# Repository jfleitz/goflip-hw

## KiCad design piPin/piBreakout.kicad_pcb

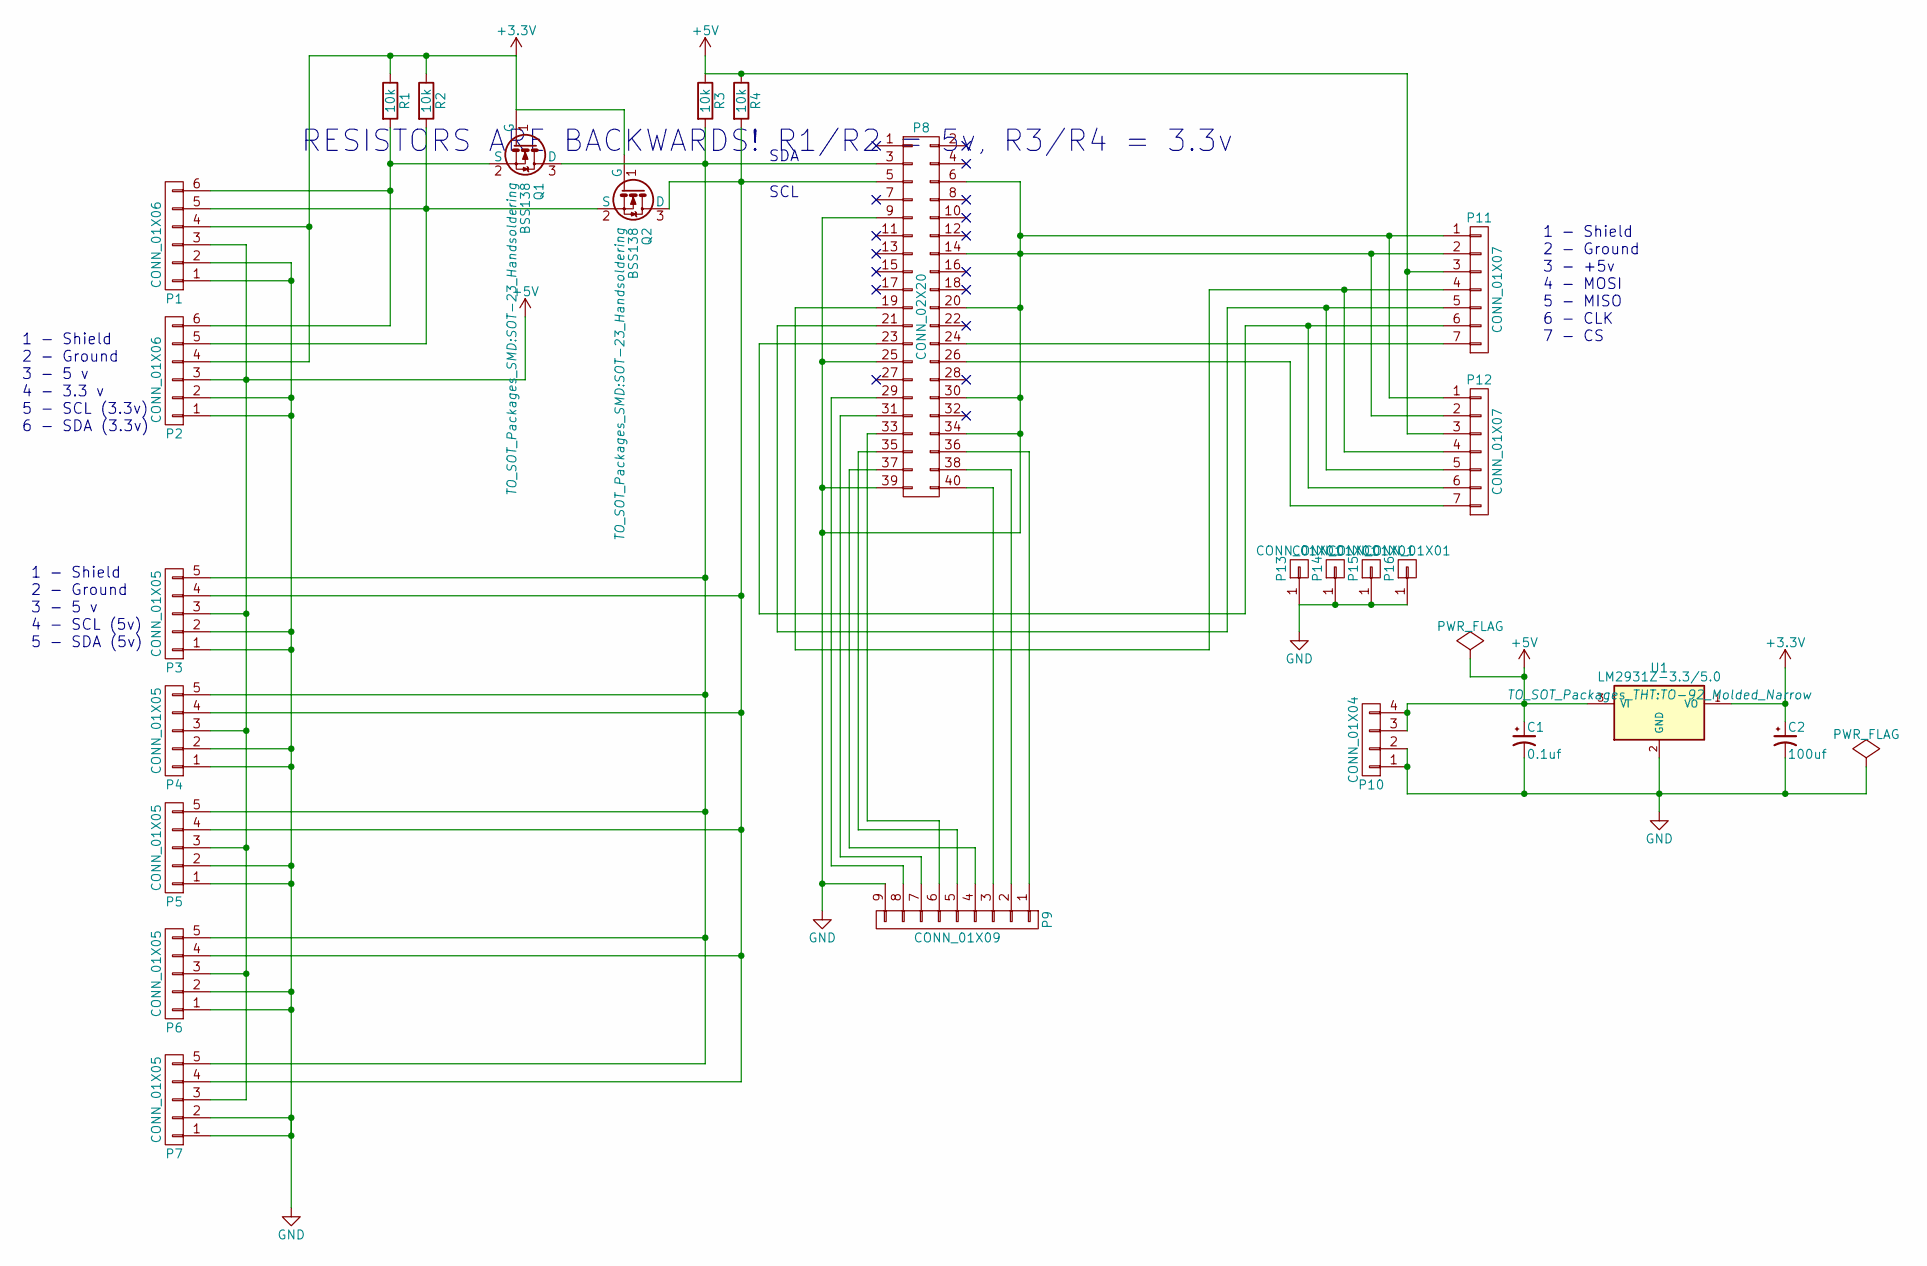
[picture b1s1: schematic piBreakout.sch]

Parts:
C1: 0.1uf; C_Radial_D5_L11_P2
C2: 100uf; C_Radial_D5_L11_P2
P1, P2: CONN_01X06; Molex_KK_6410-06
P3, P4, P5, P6, P7: CONN_01X05; Molex_KK_6410-05
P8: CONN_02X20; IDC_Header_Straight_40pins
P9: CONN_01X09; Molex_KK_6410-09
P10: CONN_01X04; Molex_KK_6410-04
P11, P12: CONN_01X07; Molex_KK_6410-07
P13, P14, P15, P16: CONN_01X01; 1pin
Q1, Q2: BSS138; SOT-23_Handsoldering
R1, R2, R3, R4: 10k; Resistor_Horizontal_RM15mm
U1: LM2931Z-3.3/5.0; TO-92_Molded_Narrow

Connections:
+3V3: C2.1, P1.4, P2.4, Q1.1 (G), Q2.1 (G), R1.1, R2.1, U1.1 (VO)
+5V: C1.1, P1.3, P2.3, P3.3, P4.3, P5.3, P6.3, P7.3, P10.3, P10.4, P11.3, P12.3, R3.1, R4.1, U1.3 (VI); also elsewhere on the board
GND: C1.2, C2.2, P1.1, P1.2, P2.1, P2.2, P3.1, P3.2, P4.1, P4.2, P5.1, P5.2, P6.1, P6.2, P7.1, P7.2, P8.6, P8.9, P8.14, P8.20, P8.25, P8.30, P8.34, P8.39, P9.9, P10.1, P10.2, P11.1, P11.2, P12.1, P12.2, P13.1, P14.1, P15.1, P16.1, U1.2 (GND); also elsewhere on the board
unnamed: P1.5, P2.5, Q2.2 (S), R2.2
unnamed: P1.6, P2.6, Q1.2 (S), R1.2
unnamed: P3.4, P4.4, P5.4, P6.4, P7.4, P8.5, Q2.3 (D), R4.2
unnamed: P3.5, P4.5, P5.5, P6.5, P7.5, P8.3, Q1.3 (D), R3.2
unnamed 23: P8.29, P9.8; also elsewhere on the board
unnamed 24: P8.31, P9.7; also elsewhere on the board
unnamed 26: P8.33, P9.6; also elsewhere on the board
unnamed 27: P8.35, P9.5; also elsewhere on the board
unnamed 28: P8.36, P9.1; also elsewhere on the board
unnamed 29: P8.37, P9.4; also elsewhere on the board
unnamed 30: P8.38, P9.2; also elsewhere on the board
unnamed 31: P8.40, P9.3; also elsewhere on the board
unnamed: P8.19, P11.4, P12.4
unnamed: P8.21, P11.5, P12.5
unnamed: P8.23, P11.6, P12.6
unnamed: P8.24, P11.7
unnamed: P8.26, P12.7

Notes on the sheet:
1 - Shield 2 - Ground 3 - +5v 4 - MOSI 5 - MISO 6 - CLK 7 - CS
1 - Shield 2 - Ground 3 - 5 v 4 - 3.3 v 5 - SCL (3.3v) 6 - SDA (3.3v)
1 - Shield 2 - Ground 3 - 5 v 4 - SCL (5v) 5 - SDA (5v)
SDA
SCL
RESISTORS ARE BACKWARDS! R1/R2 = 5v, R3/R4 = 3.3v

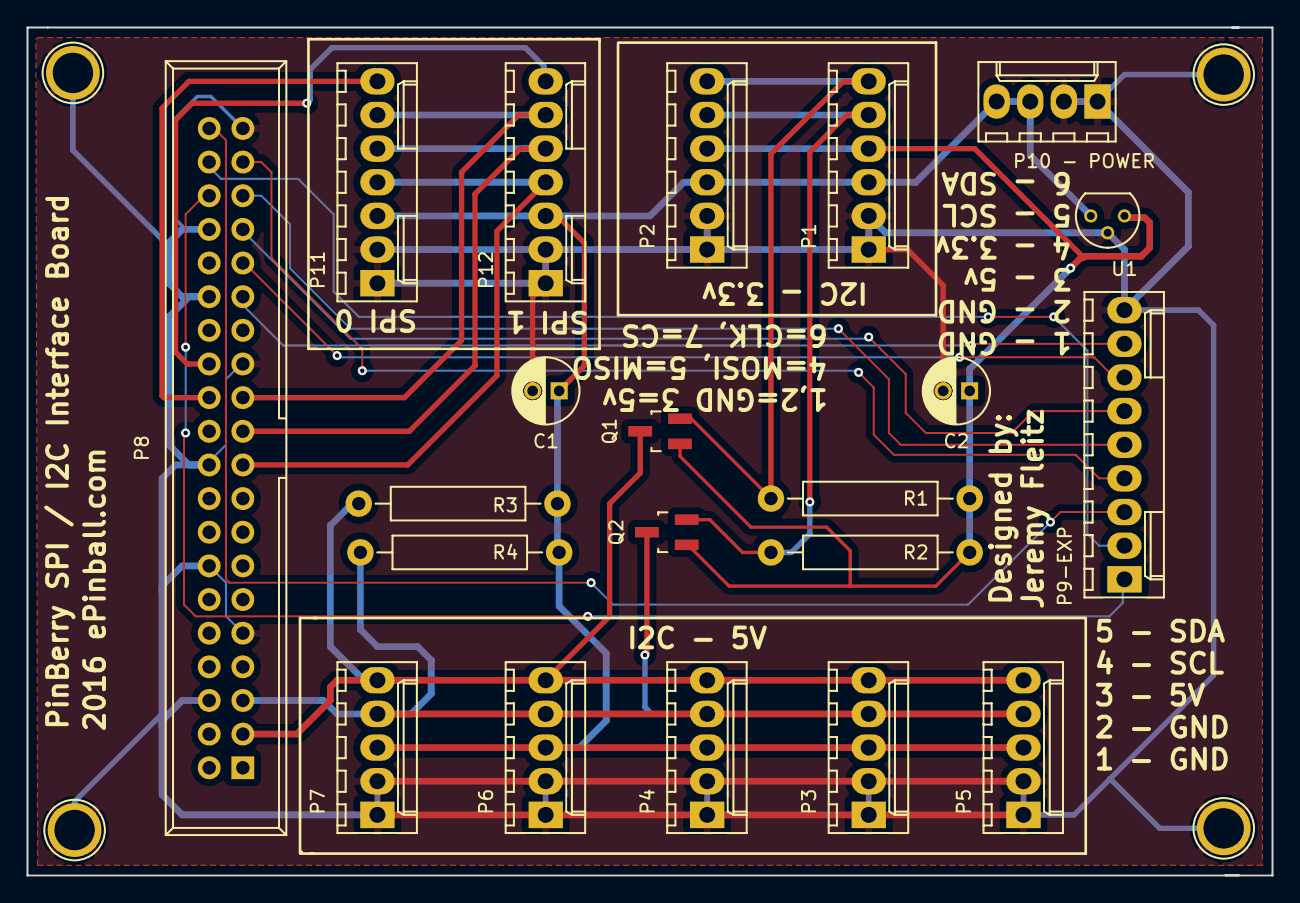
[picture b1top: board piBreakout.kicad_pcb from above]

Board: 2 copper layers, 94.0 x 64.0 mm, 25 parts (0 on the bottom side), 20 nets.

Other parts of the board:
P9-EXP: CONN_01X09; Molex_KK_6410-09
P10 - POWER: POWER; Molex_KK_6410-04

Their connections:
+5V: P10 - POWER.3, P10 - POWER.4; also elsewhere on the board
GND: P9-EXP.9, P10 - POWER.1, P10 - POWER.2; also elsewhere on the board
unnamed 23: P9-EXP.8; also elsewhere on the board
unnamed 24: P9-EXP.7; also elsewhere on the board
unnamed 26: P9-EXP.6; also elsewhere on the board
unnamed 27: P9-EXP.5; also elsewhere on the board
unnamed 28: P9-EXP.1; also elsewhere on the board
unnamed 29: P9-EXP.4; also elsewhere on the board
unnamed 30: P9-EXP.2; also elsewhere on the board
unnamed 31: P9-EXP.3; also elsewhere on the board

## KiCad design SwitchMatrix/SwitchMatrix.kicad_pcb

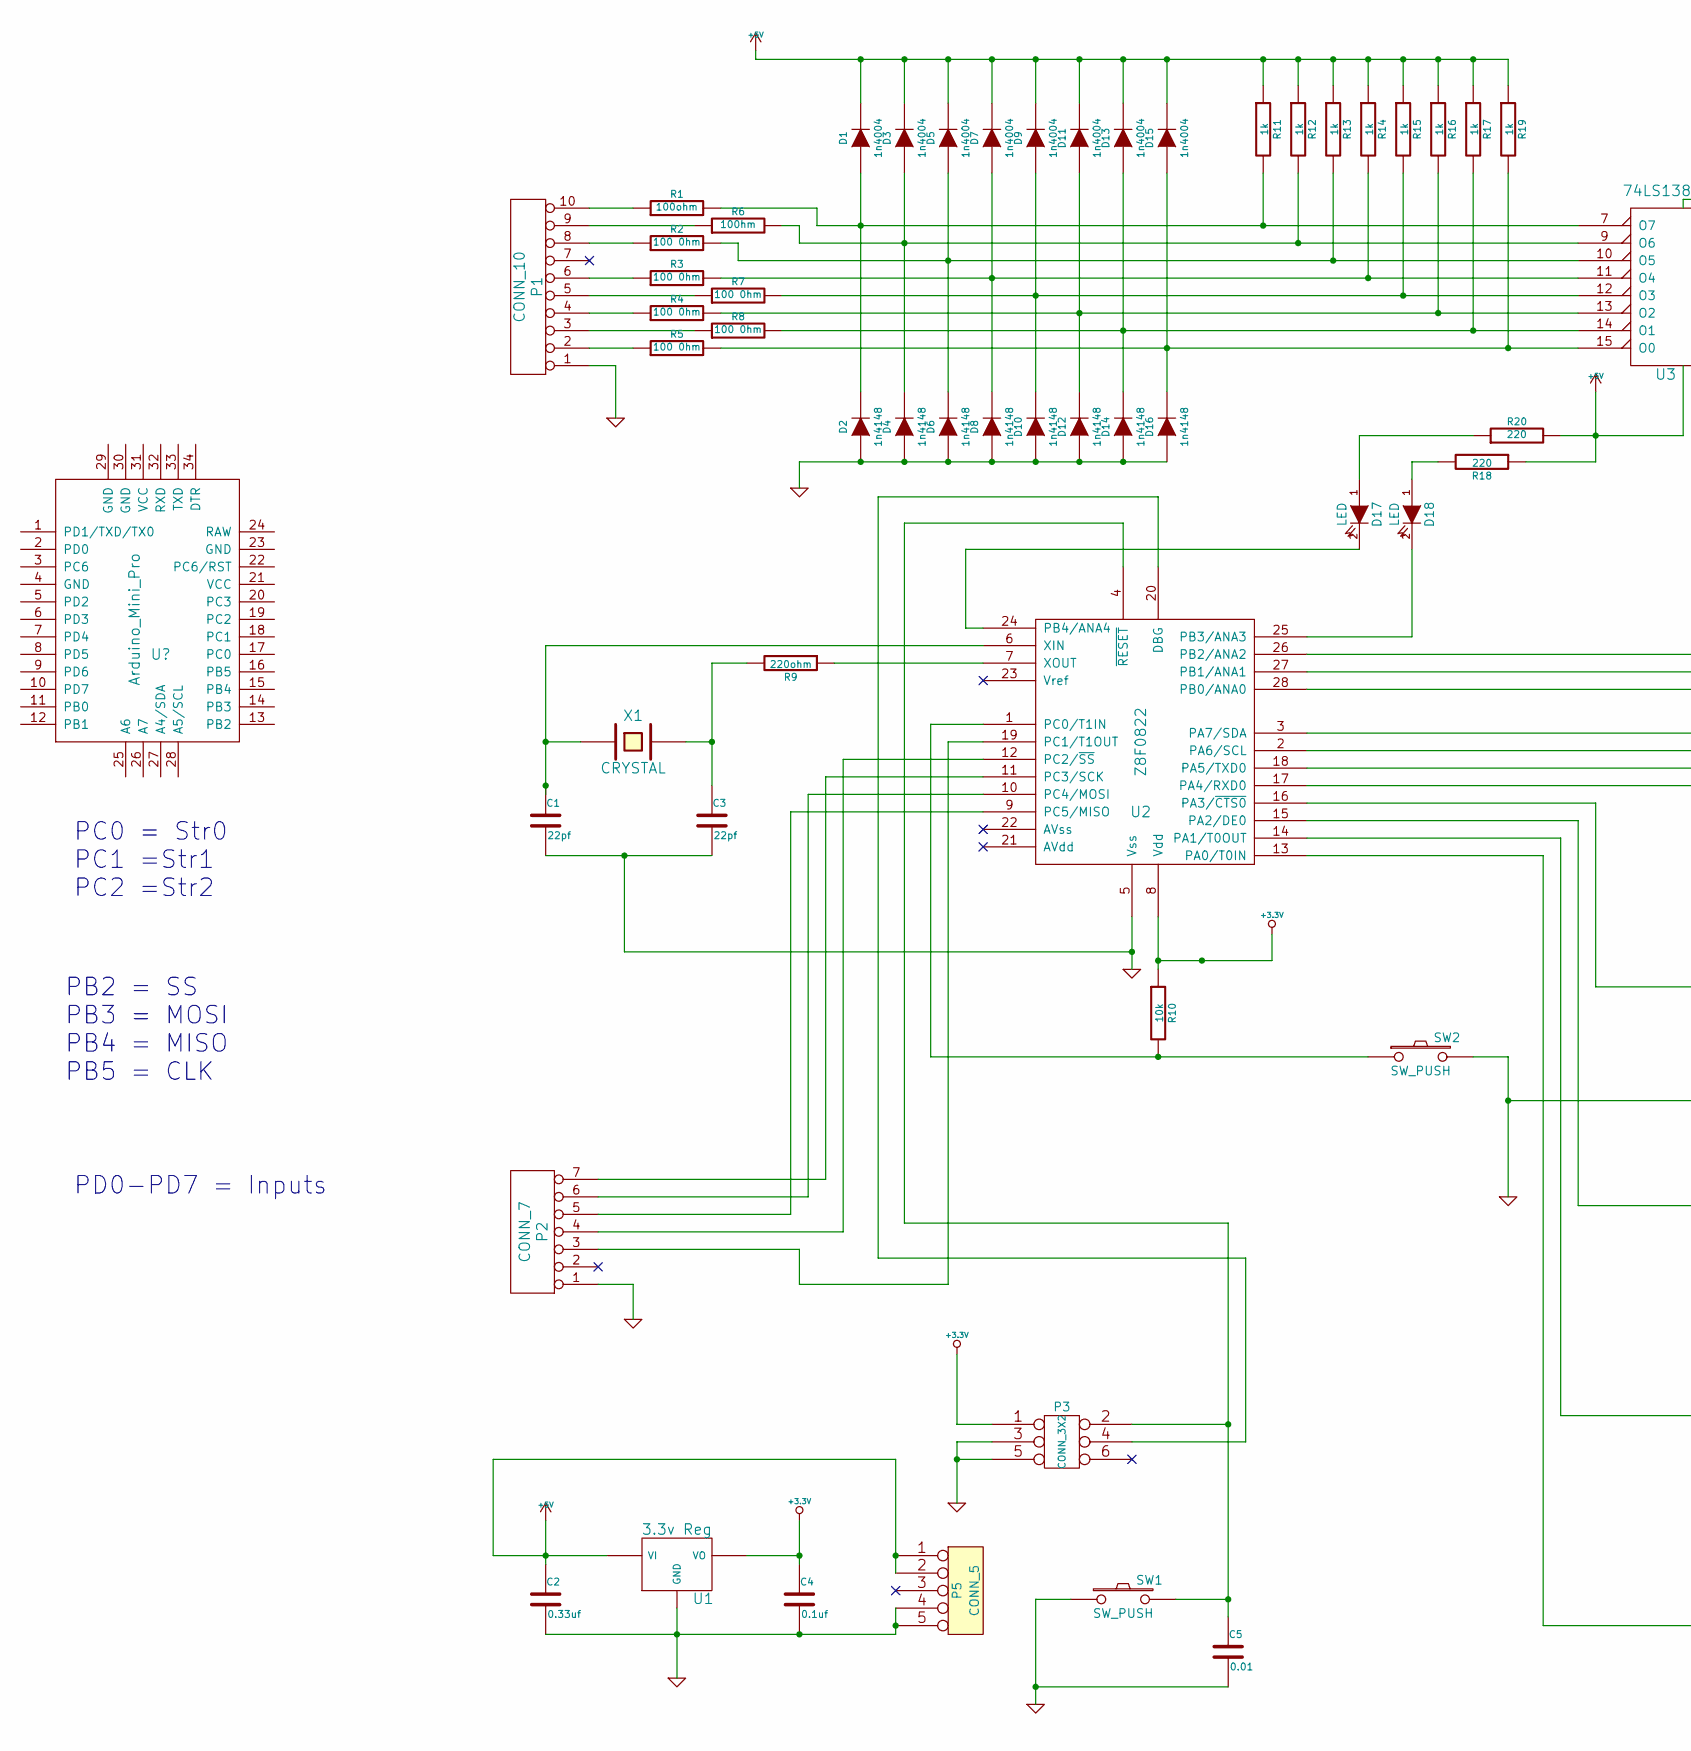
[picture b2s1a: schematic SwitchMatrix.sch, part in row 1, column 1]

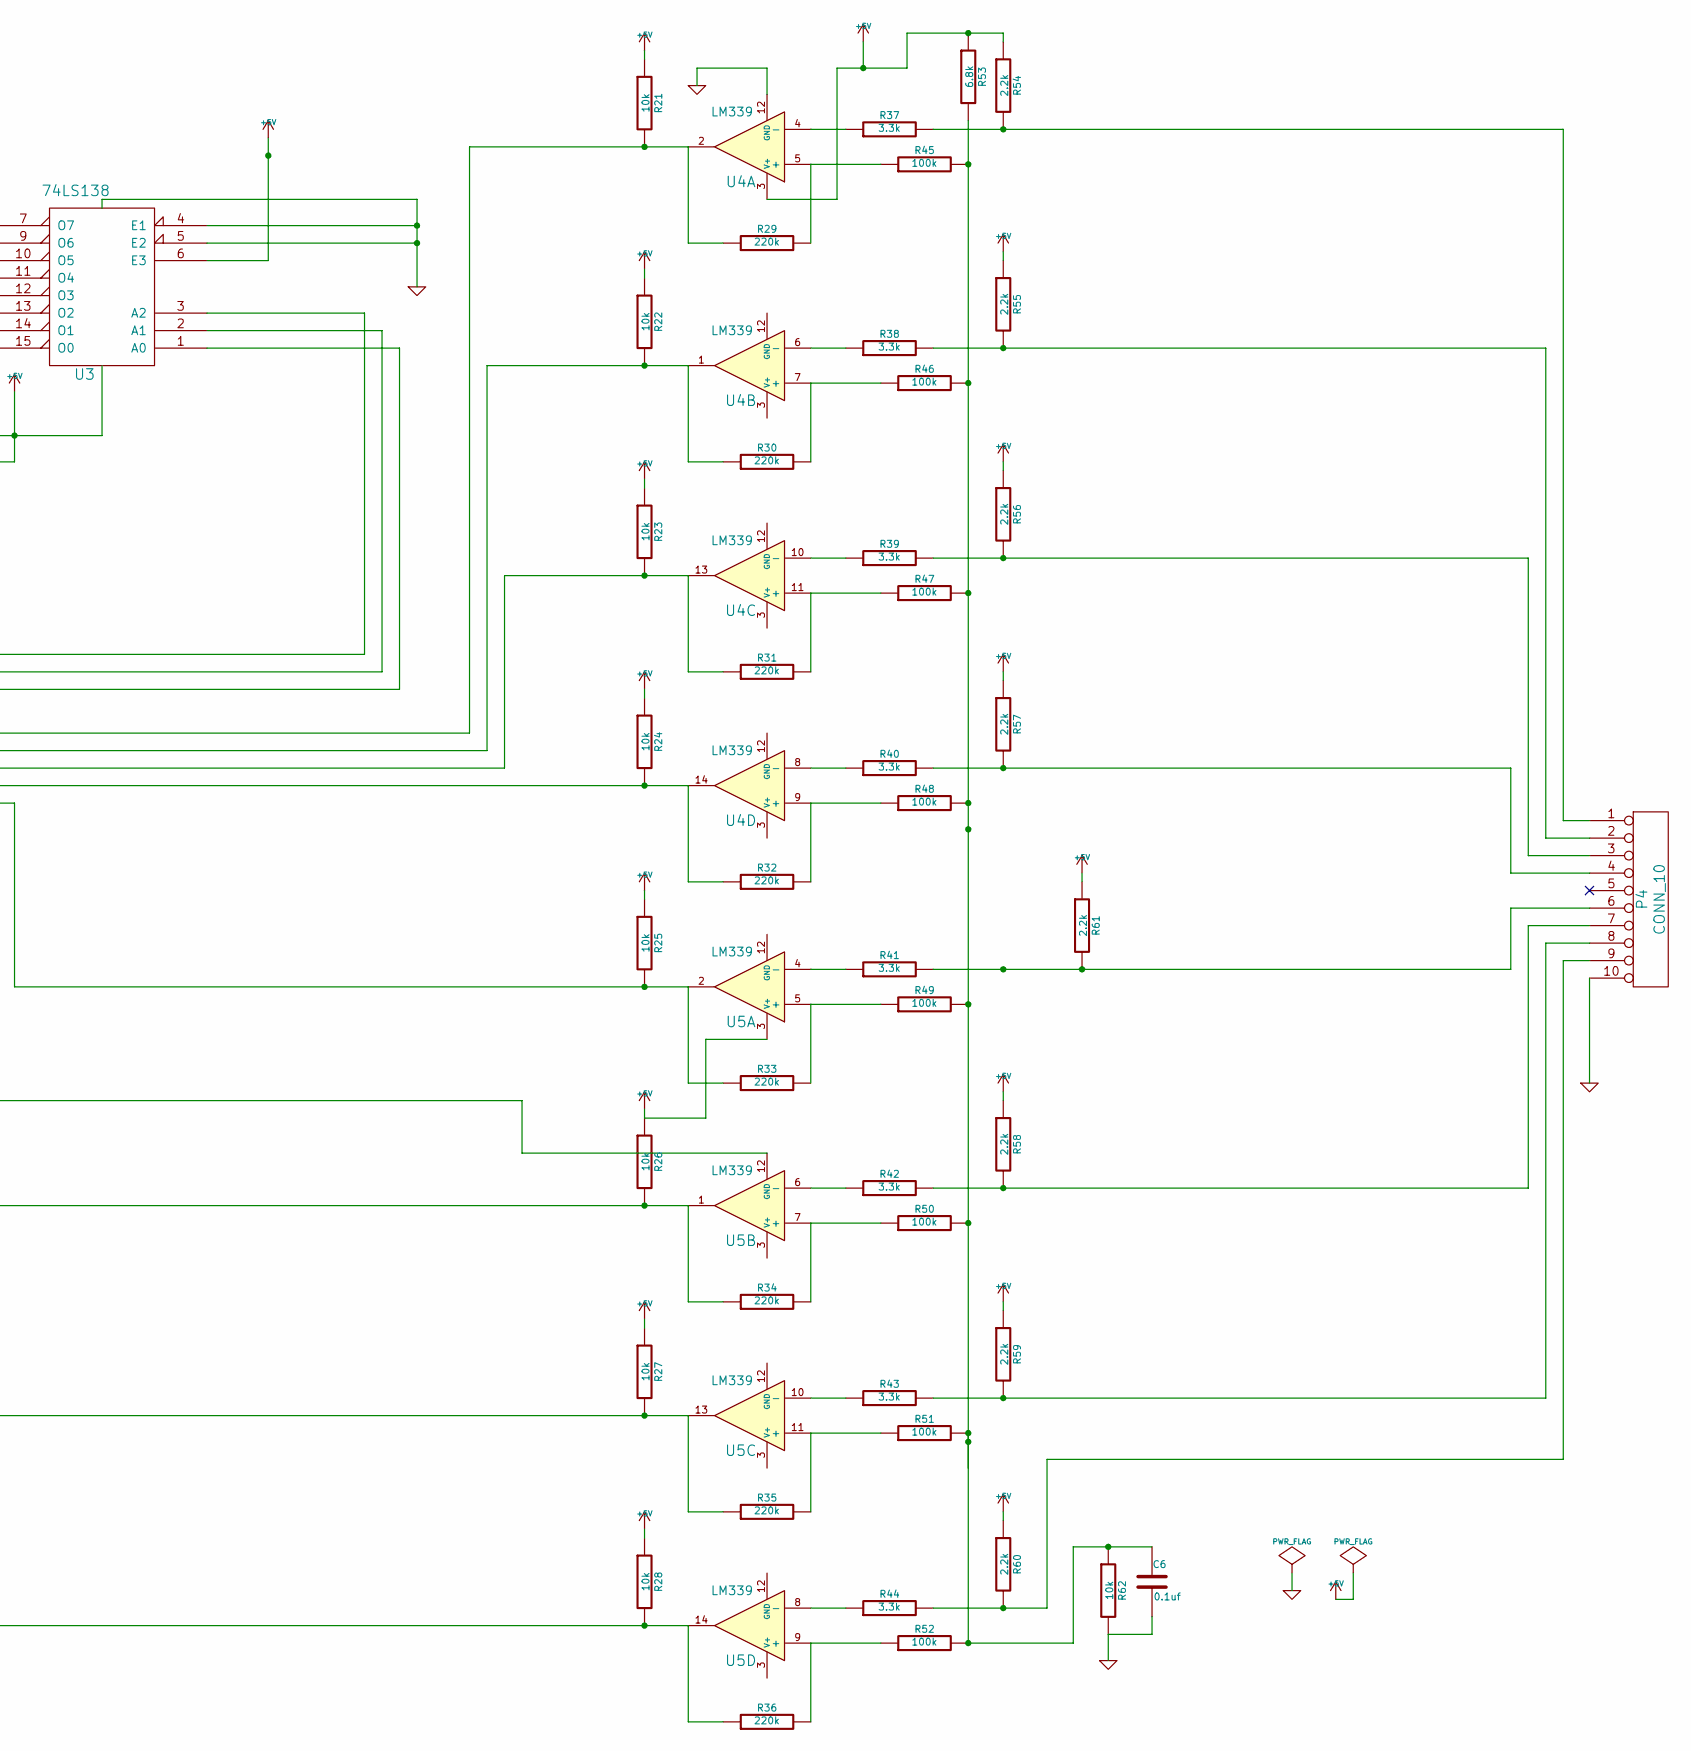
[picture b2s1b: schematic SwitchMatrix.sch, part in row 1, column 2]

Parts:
C1, C3: 22pf
C2: 0.33uf
C4, C6: 0.1uf
C5: 0.01
D1, D3, D5, D7, D9, D11, D13, D15: 1n4004
D2, D4, D6, D8, D10, D12, D14, D16: 1n4148
D17, D18: LED
P1, P4: CONN_10
P2: CONN_7
P3: CONN_3X2
P5: CONN_5
R1: 100ohm
R2, R3, R4, R5, R7, R8: 100 0hm
R6: 100hm
R9: 220ohm
R10, R21, R22, R23, R24, R25, R26, R27, R28, R62: 10k
R11, R12, R13, R14, R15, R16, R17, R19: 1k
R18, R20: 220
R29, R30, R31, R32, R33, R34, R35, R36: 220k
R37, R38, R39, R40, R41, R42, R43, R44: 3.3k
R45, R46, R47, R48, R49, R50, R51, R52: 100k
R53: 6.8k
R54, R55, R56, R57, R58, R59, R60, R61: 2.2k
SW1, SW2: SW_PUSH
U1: 3.3v Reg
U2: Z8F0822
U3: 74LS138
U4, U5: LM339
X1: CRYSTAL

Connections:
+3.3V: C4.1, P3.1, R10.1, U1.2 (VO), U2.8 (Vdd)
+5V: C2.1, D1.2 (K), D3.2 (K), D5.2 (K), D7.2 (K), D9.2 (K), D11.2 (K), D13.2 (K), D15.2 (K), P5.1, P5.2, R11.1, R12.1, R13.1, R14.1, R15.1, R16.1, R17.1, R18.1, R19.1, R20.2, R21.1, R22.1, R23.1, R24.1, R25.1, R26.1, R27.1, R28.1, R53.1, R54.1, R55.1, R56.1, R57.1, R58.1, R59.1, R60.1, R61.1, U1.1 (VI), U3.6 (E3), U3.16 (VCC), U4.3 (V+), U5.3 (V+)
GND: C1.2, C2.2, C3.2, C4.2, C5.2, C6.2, D2.1 (A), D4.1 (A), D6.1 (A), D8.1 (A), D10.1 (A), D12.1 (A), D14.1 (A), D16.1 (A), P1.1, P2.1, P3.3, P3.5, P4.10, P5.4, P5.5, R62.2, SW1.1, SW2.2, U1.3 (GND), U2.5 (Vss), U3.4 (E1), U3.5 (E2), U3.8 (GND), U4.12 (GND), U5.12 (GND)
unnamed: P1.10, R1.1
unnamed: P1.9, R6.1
unnamed: P1.8, R2.1
unnamed: P1.6, R3.1
unnamed: P1.5, R7.1
unnamed: P1.4, R4.1
unnamed: P1.3, R8.1
unnamed: P1.2, R5.1
unnamed: D7.1 (A), D8.2 (K), R3.2, R14.2, U3.11 (O4)
unnamed: D9.1 (A), D10.2 (K), R7.2, R15.2, U3.12 (O3)
unnamed: D11.1 (A), D12.2 (K), R4.2, R16.2, U3.13 (O2)
unnamed: D13.1 (A), D14.2 (K), R8.2, R17.2, U3.14 (O1)
unnamed: D15.1 (A), D16.2 (K), R5.2, R19.2, U3.15 (O0)
unnamed: D1.1 (A), D2.2 (K), R1.2, R11.2, U3.7 (O7)
unnamed: D3.1 (A), D4.2 (K), R6.2, R12.2, U3.9 (O6)
unnamed: D5.1 (A), D6.2 (K), R2.2, R13.2, U3.10 (O5)
unnamed: R33.2, R49.1, U5.5 (+)
unnamed: R44.1, U5.8 (-)
unnamed: R36.2, R52.1, U5.9 (+)
unnamed: R35.2, R51.1, U5.11 (+)
unnamed: R40.1, U4.8 (-)
unnamed: R32.2, R48.1, U4.9 (+)
unnamed: R41.1, U5.4 (-)
unnamed: R42.1, U5.6 (-)
unnamed: R34.2, R50.1, U5.7 (+)
unnamed: R43.1, U5.10 (-)
unnamed: C5.1, P3.2, SW1.2, U2.4 (~RESET)
unnamed: R9.1, U2.7 (XOUT)
unnamed: D18.1 (A), R18.2
unnamed: D17.1 (A), R20.1
unnamed: D18.2 (K), U2.25 (PB3/ANA3)
unnamed: D17.2 (K), U2.24 (PB4/ANA4)
unnamed: P2.3, U2.19 (PC1/T1OUT)
unnamed: U2.27 (PB1/ANA1), U3.2 (A1)
unnamed: U2.26 (PB2/ANA2), U3.3 (A2)
unnamed: U2.28 (PB0/ANA0), U3.1 (A0)
unnamed: C3.1, R9.2, X1.2
unnamed: P2.7, U2.11 (PC3/SCK)
unnamed: P2.6, U2.10 (PC4/MOSI)
unnamed: P2.5, U2.9 (PC5/MISO)
unnamed: P2.4, U2.12 (PC2/~SS)
unnamed: P3.4, U2.20 (DBG)
unnamed: R27.2, R35.1, U2.14 (PA1/T0OUT), U5.13
unnamed: P4.8, R43.2, R59.2
unnamed: R28.2, R36.1, U2.13 (PA0/T0IN), U5.14
unnamed: R25.2, R33.1, U2.16 (PA3/~CTS0), U5.2
unnamed: P4.6, R41.2, R61.2
unnamed: R26.2, R34.1, U2.15 (PA2/DE0), U5.1
unnamed: P4.9, R44.2, R60.2
unnamed: P4.7, R42.2, R58.2
unnamed: R37.1, U4.4 (-)
unnamed: R29.2, R45.1, U4.5 (+)
unnamed: R21.2, R29.1, U2.3 (PA7/SDA), U4.2
unnamed: P4.1, R37.2, R54.2
unnamed: R38.1, U4.6 (-)
unnamed: R30.2, R46.1, U4.7 (+)
unnamed: P4.4, R40.2, R57.2
unnamed: R24.2, R32.1, U2.17 (PA4/RXD0), U4.14
unnamed: R22.2, R30.1, U2.2 (PA6/SCL), U4.1
unnamed: P4.2, R38.2, R55.2
unnamed: R39.1, U4.10 (-)
unnamed: R31.2, R47.1, U4.11 (+)
unnamed: C6.1, R45.2, R46.2, R47.2, R48.2, R49.2, R50.2, R51.2, R52.2, R53.2, R62.1
unnamed: R23.2, R31.1, U2.18 (PA5/TXD0), U4.13
unnamed: P4.3, R39.2, R56.2
unnamed: C1.1, U2.6 (XIN), X1.1
unnamed: R10.2, SW2.1, U2.1 (PC0/T1IN)

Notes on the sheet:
PB2 = SS PB3 = MOSI PB4 = MISO PB5 = CLK
PC0 = Str0 PC1 =Str1 PC2 =Str2
PD0-PD7 = Inputs

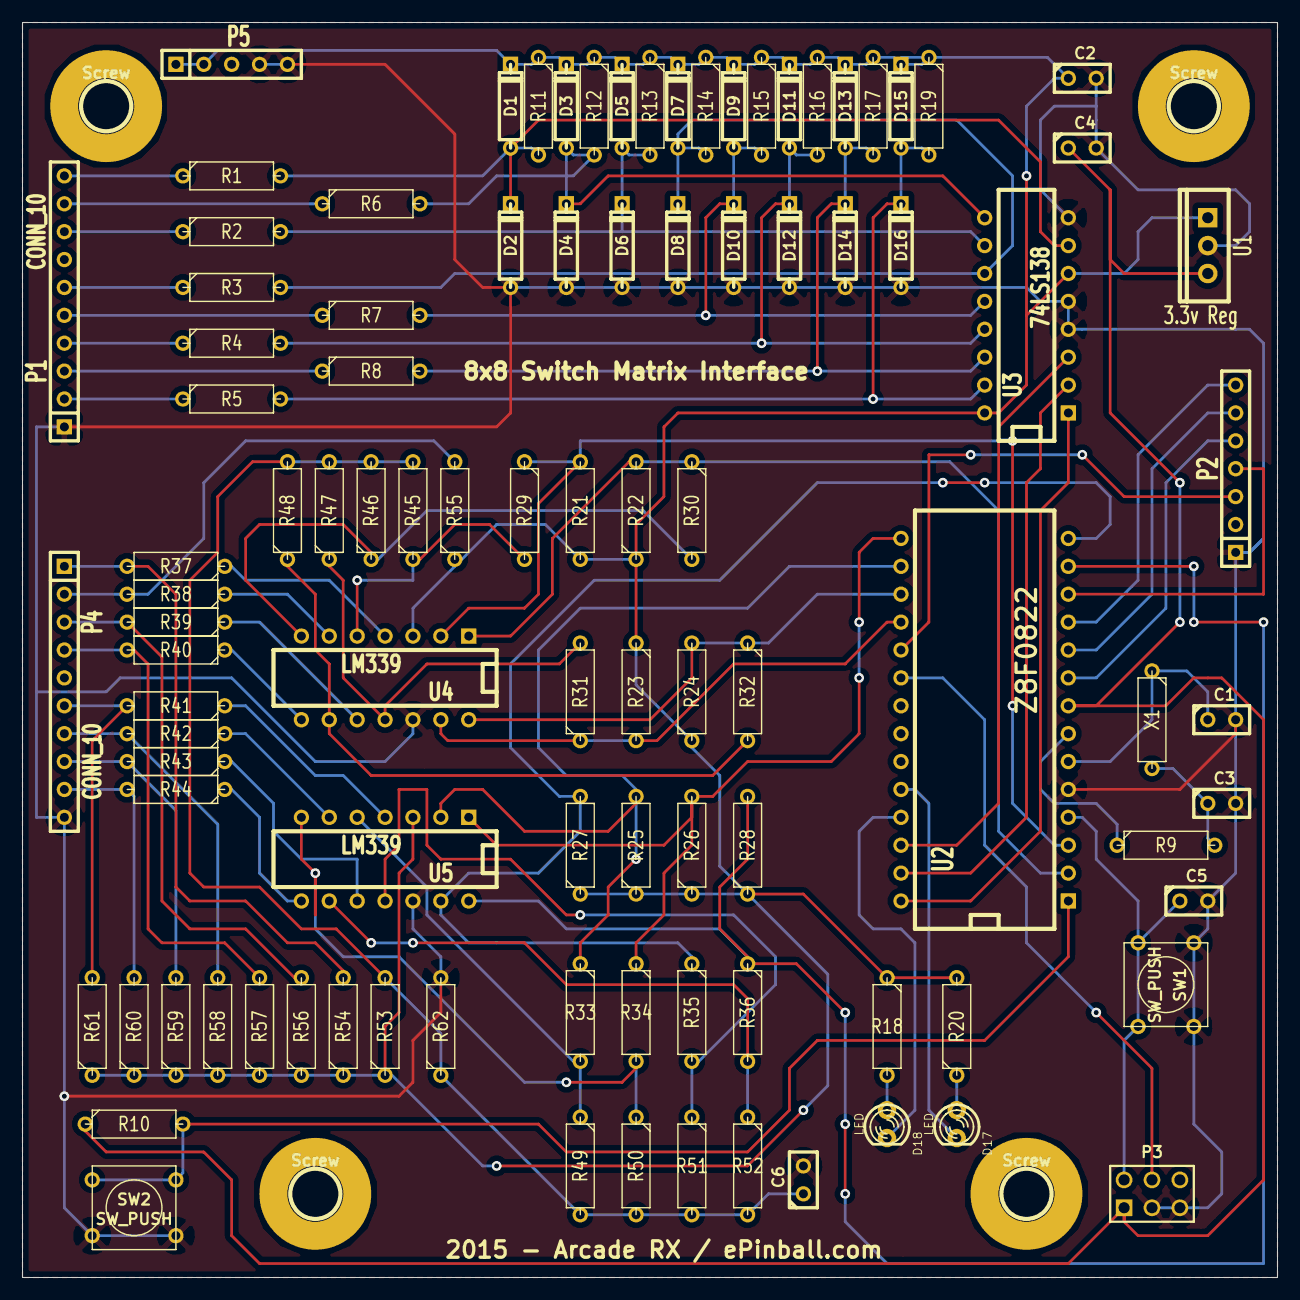
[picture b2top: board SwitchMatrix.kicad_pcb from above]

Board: 2 copper layers, 114.3 x 114.3 mm, 103 parts (0 on the bottom side), 70 nets.

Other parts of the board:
Screw: P***; Hole
Screw#2, Screw#3, Screw#4: P***; Hole

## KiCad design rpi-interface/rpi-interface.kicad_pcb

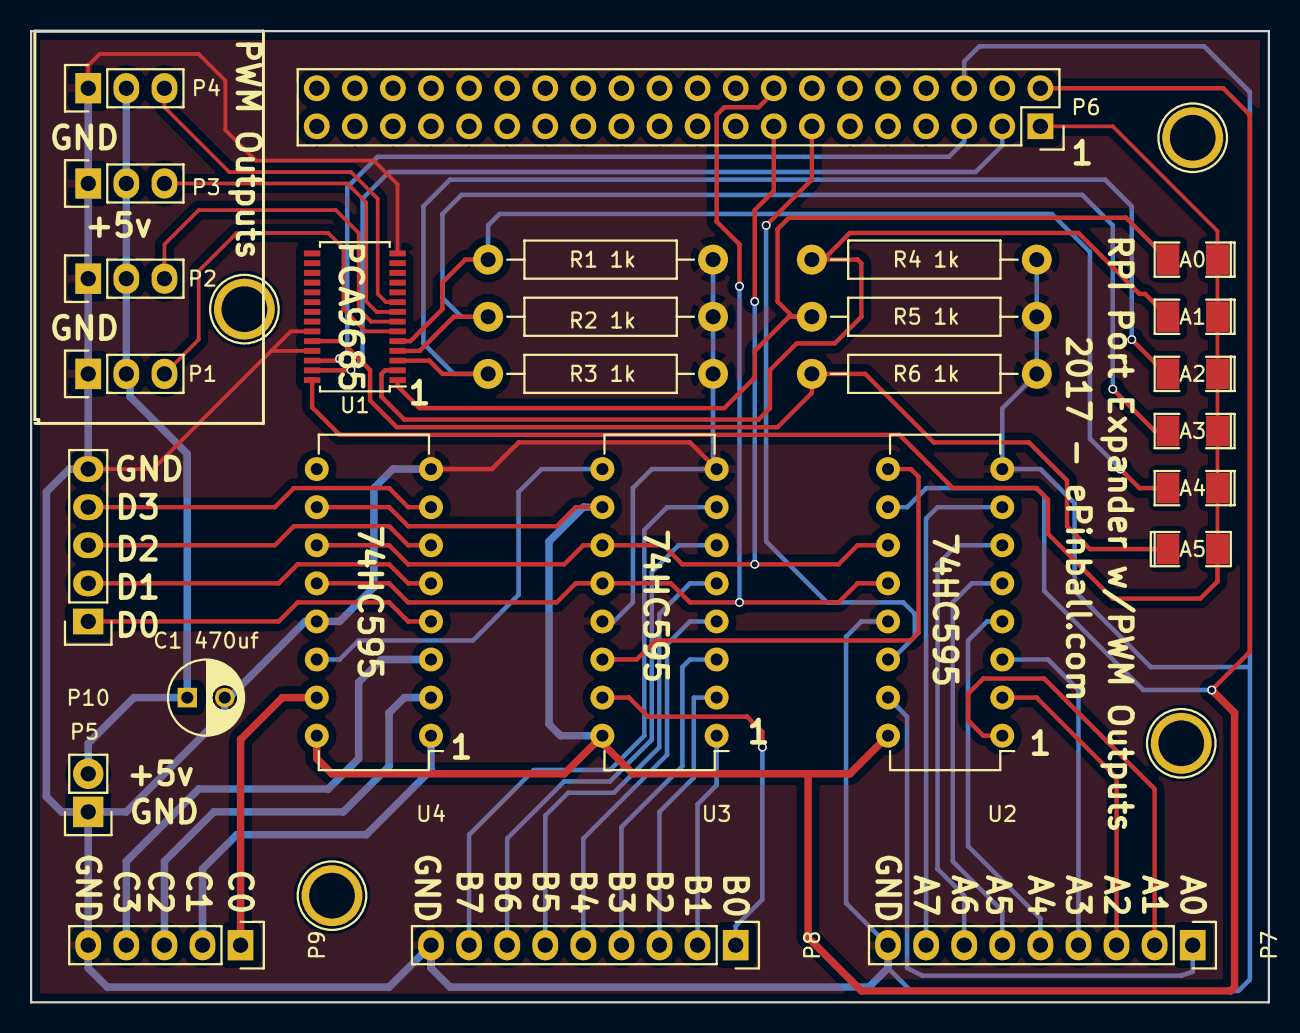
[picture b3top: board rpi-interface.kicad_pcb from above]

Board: 2 copper layers, 82.6 x 64.8 mm, 27 parts (0 on the bottom side), 45 nets.

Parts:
A0: Addr A0; SMD-1206_Pol
A1: Addr A1; SMD-1206_Pol
A2: Addr A2; SMD-1206_Pol
A3: Addr A3; SMD-1206_Pol
A4: Addr A4; SMD-1206_Pol
A5: Addr A5; SMD-1206_Pol
C1 470uf: 470uf; C_Radial_D5_L11_P2.5
P1: PWM1; Pin_Header_Straight_1x03
P2: PWM2; Pin_Header_Straight_1x03
P3: PWM3; Pin_Header_Straight_1x03
P4: PWM4; Pin_Header_Straight_1x03
P5: Servo Power; Pin_Header_Straight_1x02
P6: GPIO Connector; Socket_Strip_Straight_2x20
P7: Out A; Pin_Header_Straight_1x09
P8: Out B; Pin_Header_Straight_1x09
P9: Out C; Pin_Header_Straight_1x05
P10: Out D; Pin_Header_Straight_1x05
R1 1k, R2 1k, R3 1k, R4 1k, R5 1k, R6 1k: 1k; Resistor_Horizontal_RM15mm
U1: PCA9685; TSSOP-28_4.4x9.7mm_Pitch0.65mm
U2, U3, U4: 74HC595; DIP-16_W7.62mm

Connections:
+3V3: A0.1, A1.1, A2.1, A3.1, A4.1, A5.2, P6.1, U1.28
+5V: P6.2, U2.10, U2.16, U3.10, U3.16, U4.10, U4.16
GND: C1 470uf.2, P1.1, P2.1, P3.1, P4.1, P5.1, P6.6, P7.9, P8.9, P9.5, P10.5, R1 1k.2, R2 1k.2, R3 1k.2, R4 1k.2, R5 1k.2, R6 1k.2, U1.14, U1.23, U1.25, U2.8, U2.13, U3.8, U3.13, U4.8, U4.13
unnamed: A0.2, R5 1k.1, U1.1
unnamed: A1.2, R4 1k.1, U1.2
unnamed: A2.2, R3 1k.1, U1.3
unnamed: A3.2, R2 1k.1, U1.4
unnamed: A4.2, R1 1k.1, U1.5
unnamed: A5.1, R6 1k.1, U1.24
unnamed: C1 470uf.1, P1.2, P2.2, P3.2, P4.2, P5.2
unnamed: P1.3, U1.6
unnamed: P2.3, U1.7
unnamed: P3.3, U1.8
unnamed: P4.3, U1.9
unnamed: P6.3, U1.27
unnamed: P6.5, U1.26
unnamed: P6.13, U2.14
unnamed: P6.15, U2.11, U3.11, U4.11
unnamed: P6.16, U2.12, U3.12, U4.12
unnamed: P7.1, U2.15
unnamed: P7.2, U2.1
unnamed: P7.3, U2.2
unnamed: P7.4, U2.3
unnamed: P7.5, U2.4
unnamed: P7.6, U2.5
unnamed: P7.7, U2.6
unnamed: P7.8, U2.7
unnamed: P8.1, U3.15
unnamed: P8.2, U3.1
unnamed: P8.3, U3.2
unnamed: P8.4, U3.3
unnamed: P8.5, U3.4
unnamed: P8.6, U3.5
unnamed: P8.7, U3.6
unnamed: P8.8, U3.7
unnamed: P9.1, U4.15
unnamed: P9.2, U4.1
unnamed: P9.3, U4.2
unnamed: P9.4, U4.3
unnamed: P10.1, U4.4
unnamed: P10.2, U4.5
unnamed: P10.3, U4.6
unnamed: P10.4, U4.7
unnamed: U2.9, U3.14
unnamed: U3.9, U4.14

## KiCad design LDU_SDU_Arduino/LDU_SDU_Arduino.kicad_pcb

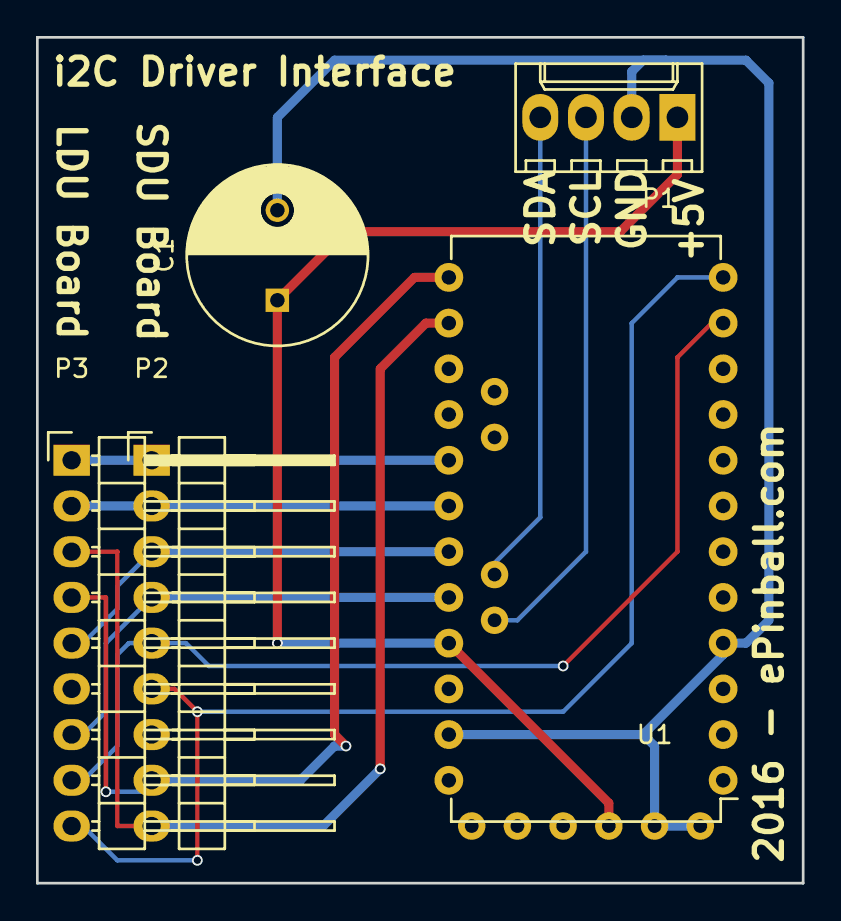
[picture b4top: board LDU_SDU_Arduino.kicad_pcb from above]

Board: 2 copper layers, 42.5 x 47.0 mm, 5 parts (0 on the bottom side), 12 nets.

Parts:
C1: CP; C_Radial_D10_L13_P5
P1: CONN_01X04; Molex_KK_6410-04
P2: SDU; Pin_Header_Angled_1x09
P3: LDU; Pin_Header_Angled_1x09
U1: Arduino_Mini_Pro; MiniPro

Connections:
+5V: C1.1, P1.1, U1.21, U1.31
Earth: C1.2, P1.2, U1.4, U1.23, U1.29, U1.30
unnamed: P1.3, U1.28
unnamed: P1.4, U1.27
unnamed: P2.1, P3.1, U1.17
unnamed: P2.2, P3.2, U1.18
unnamed: P2.3, P3.5, U1.19
unnamed: P2.4, P3.7, U1.20
unnamed: P2.5, P3.8, U1.11
unnamed: P2.6, P3.9, U1.12
unnamed: P2.8, P3.4, U1.13
unnamed: P2.9, P3.3, U1.14

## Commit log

2018-02-27 copy from dropbox
